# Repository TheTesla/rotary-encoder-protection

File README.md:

# Rotary Encoder Protection Board

The rotary encoders don't have any electrical protection mechanism. Overcurrent into the open collector outputs will damage them.

This board protects the rotary encoder against reverse polarity and short overvoltage spikes on the power supply line. Each data line is protected using a 10k resistor in series. Pull-up resistors are incooperated on the encoder side. That means, the board outputs are directly high impedance logic level. External voltage to these data pins won't damage the encoder or protection board.

Direct connection to ICs with a low voltage tolerance at the inputs is possible, because the clamp diodes in the IC will limit the voltage from the high impedance outputs of the board. 

## Associated Projects

That protection board is part of the plug at the rotary encoder cable. It is intended to be connected to the logic board, which implements the data processing:

* https://github.com/TheTesla/OSH-CMM-LogicBoard

## Author/Contact

Stefan Helmert <stefan.helmert@htw-dresden.de>

## Appendix

### Pictures

The PCB without case and without rotary encoder:

### Schematics

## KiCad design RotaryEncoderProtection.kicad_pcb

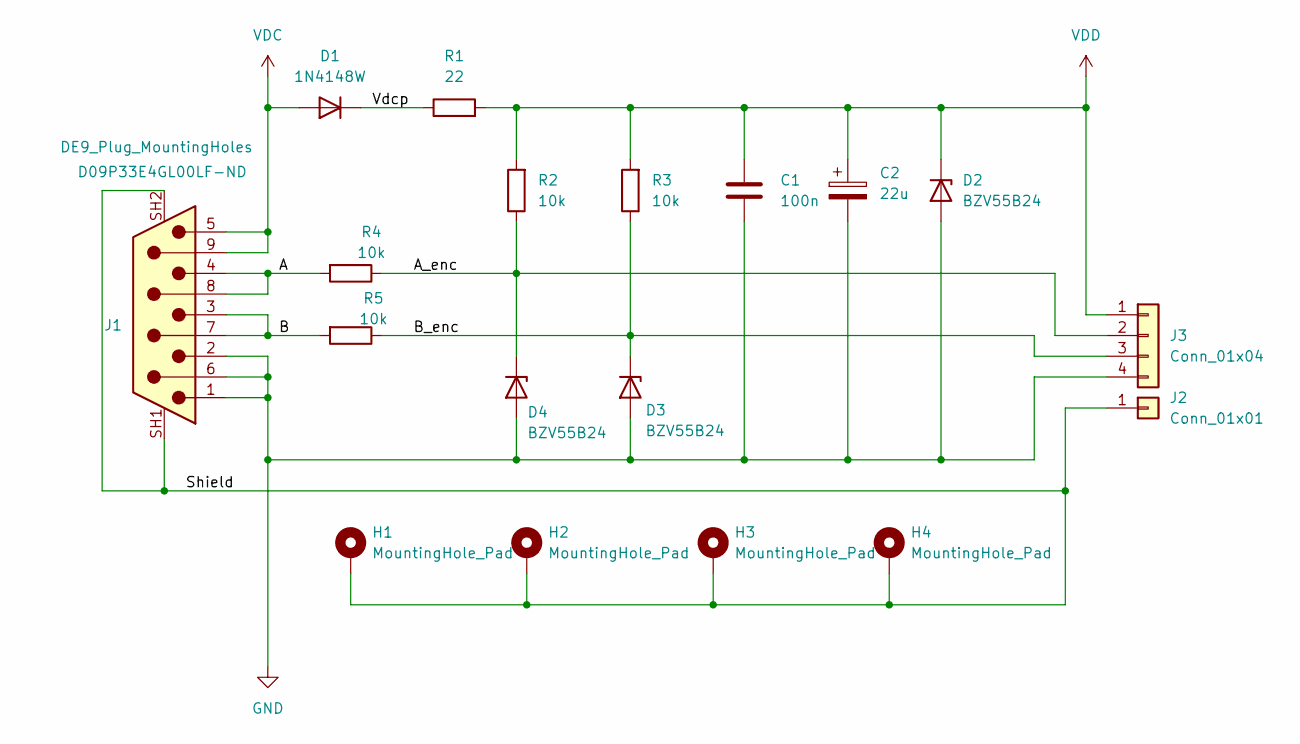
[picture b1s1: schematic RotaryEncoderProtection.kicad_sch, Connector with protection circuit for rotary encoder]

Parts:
C1: 100n; C_0805_2012Metric
C2: 22u; CP_Radial_D5.0mm_P2.00mm
D1: 1N4148W; D_SOD-123
D2, D3, D4: BZV55B24; D_MiniMELF
H1, H2, H3, H4: MountingHole_Pad; MountingHole_2.7mm_M2.5_ISO14580_Pad_TopBottom
J1: DE9_Plug_MountingHoles; AMPHENOL_D09P33E4GL00LF; Digikey.de D09P33E4GL00LF-ND
J2: Conn_01x01; SolderWire-2.5sqmm_1x01_D2.4mm_OD4.4mm
J3: Conn_01x04; SolderWire-0.75sqmm_1x04_P4.8mm_D1.25mm_OD2.3mm
R1: 22; R_0805_2012Metric
R2, R3, R4, R5: 10k; R_0805_2012Metric

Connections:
/A: J1.4, J1.8, R4.2
/A_enc: D4.1 (K), J3.2, R2.1, R4.1
/B: J1.3, J1.7, R5.2
/B_enc: D3.1 (K), J3.3, R3.1, R5.1
/Shield: H1.1, H2.1, H3.1, H4.1, J1.SH1 (PAD), J1.SH2 (PAD), J2.1
/Vdcp: D1.1 (K), R1.1
GND: C1.2, C2.2, D2.2 (A), D3.2 (A), D4.2 (A), J1.1, J1.2, J1.6, J3.4
VDC: D1.2 (A), J1.5, J1.9
VDD: C1.1, C2.1, D2.1 (K), J3.1, R1.2, R2.2, R3.2

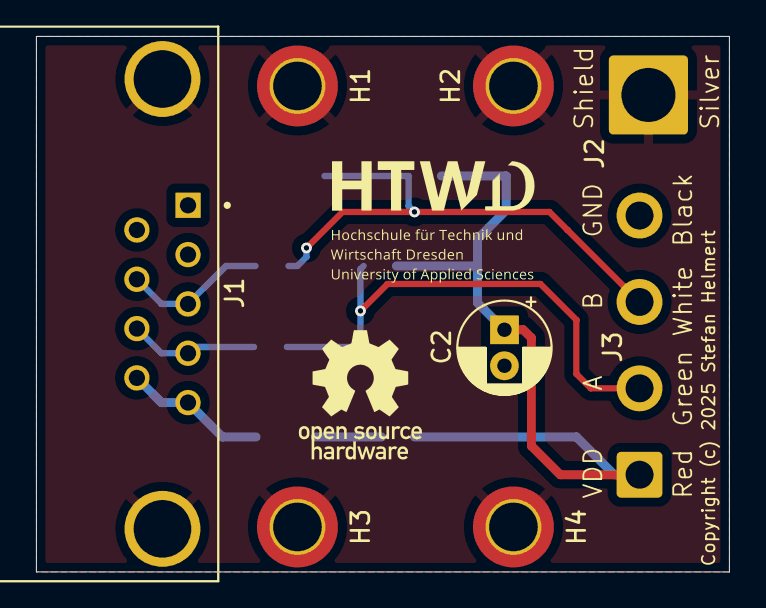
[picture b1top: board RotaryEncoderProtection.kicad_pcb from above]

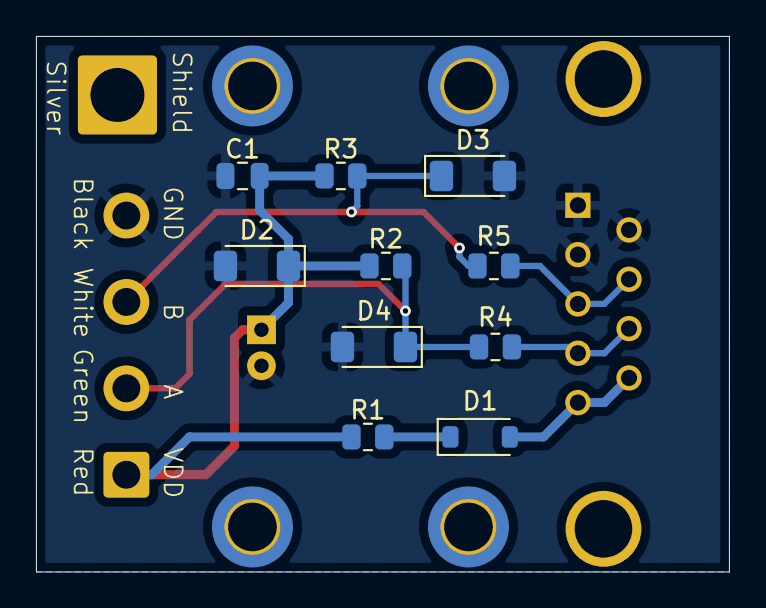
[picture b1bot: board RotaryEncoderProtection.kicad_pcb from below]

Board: 2 copper layers, 38.5 x 29.8 mm, 18 parts (10 on the bottom side), 9 nets.

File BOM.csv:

"Reference","Value","Datasheet","Footprint","Qty","DNP","Reichelt.de"
"C1","100n","~","Capacitor_SMD:C_0805_2012Metric","1","","X7R-G0805 100N"
"C2","22u","~","Capacitor_THT:CP_Radial_D5.0mm_P2.00mm","1","","RAD 22/35"
"D1","1N4148W","https://www.vishay.com/docs/85748/1n4148w.pdf","Diode_SMD:D_SOD-123","1","","1N 4148W DIO"
"D2,D3,D4","BZV55B24","https://assets.nexperia.com/documents/data-sheet/BZV55_SER.pdf","Diode_SMD:D_MiniMELF","3","","SMD ZF 24"
"J1","DE9_Plug_MountingHoles","https://cdn-reichelt.de/documents/datenblatt/C120/DBR1-MXX-L.pdf","Connector_Dsub:DSUB-9_Male_Horizontal_P2.77x2.84mm_EdgePinOffset4.94mm_Housed_MountingHolesOffset7.48mm","1","","D-SUB ST 09US"
"J2","Conn_01x01","~","Connector_Wire:SolderWire-2.5sqmm_1x01_D2.4mm_OD4.4mm","1","",""
"J3","Conn_01x04","~","Connector_Wire:SolderWire-0.75sqmm_1x04_P4.8mm_D1.25mm_OD2.3mm","1","",""
"R1","22","~","Resistor_SMD:R_0805_2012Metric","1","","SMD-0805 22,0"
"R2,R3,R4,R5","10k","~","Resistor_SMD:R_0805_2012Metric","4","","SMD-0805 10,0K"

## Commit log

2024-07-04 ready
2024-07-05 removed traces, where zones are; added text, logos, copyright; added Reichelt article numbvers
2024-07-19 optimized silkscreen
2024-07-19 added readme
2024-07-29 smaller board
2024-09-11 case for protaction board nearly ready
2024-09-12 one part of case ready
2024-09-13 added fillet
2024-11-22 construction of case for the plug is ready but not tested yet
2024-11-27 xyzcad version of case top
2024-11-27 case top looks ready
2024-11-27 more resolution; added artefact (stl)
2024-11-27 bottom case nearly ready
2024-11-27 added Freecad file to compare case to PCB; bottom case nearly ready
2024-11-27 case with rounder outer edges, fits better, single file
2024-11-27 bottom fits better
2025-03-14 Digikey M3 D-Sub-9 Connector
2025-03-14 new KiCad Standard D-Sub-9 Connector
2025-03-14 replaced Reichelt SKU for D-Sub-9 Connector
2025-04-14 OSH documentation guideline structure
2025-04-14 licenses added with reuse
2025-04-14 added some metadata in okh.toml
2025-04-14 more pictures
2025-04-23 detailed docmumentation about the functionality added
2025-04-28 added soldering and testing instractions; ToDo: testing instructions for protection of data pins
2025-04-28 menufacturing endtest instructions ready

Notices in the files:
RotaryEncoderProtection.kicad_pcb:
Copyright (c) 2025 Stefan Helmert
